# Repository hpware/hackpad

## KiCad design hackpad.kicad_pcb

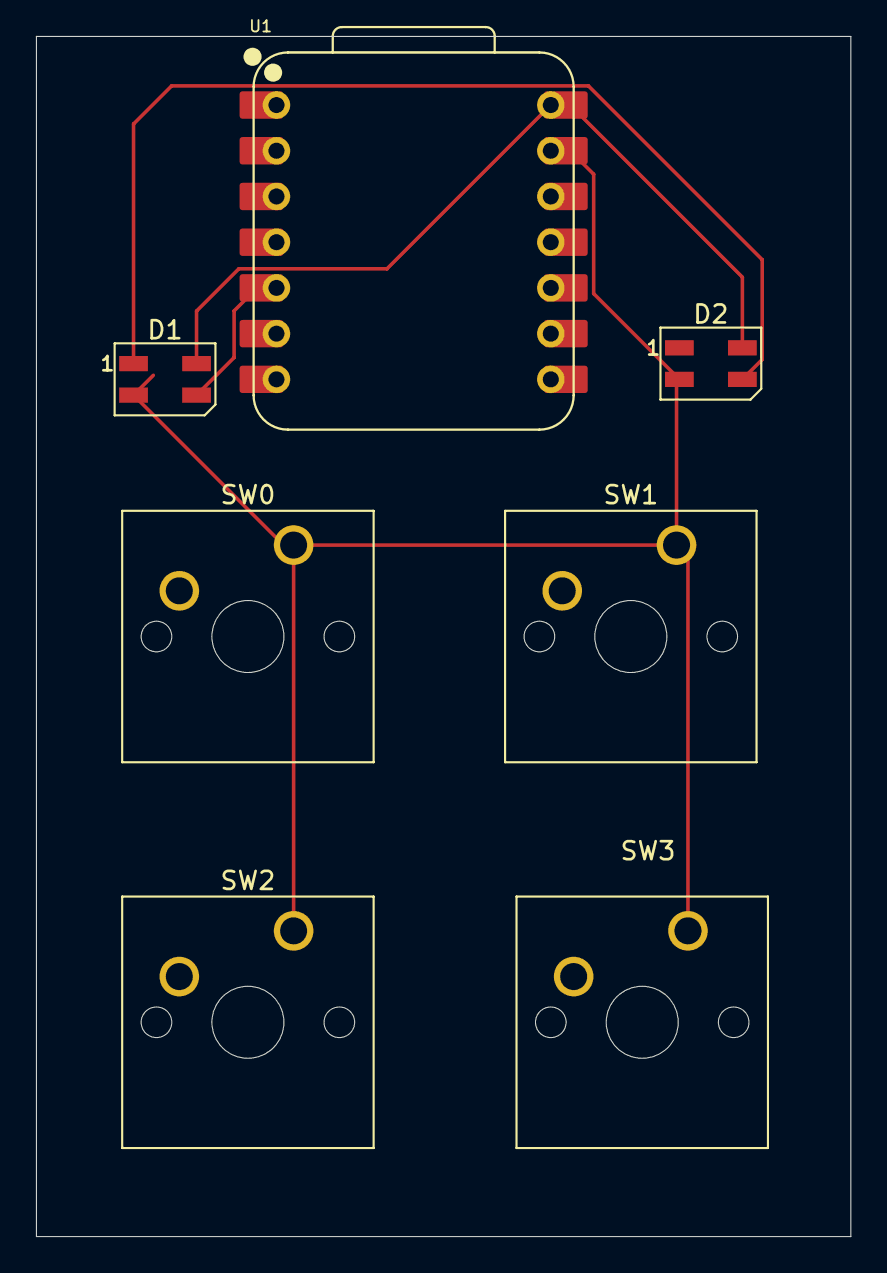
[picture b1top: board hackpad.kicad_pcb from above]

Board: 2 copper layers, 45.2 x 66.7 mm, 7 parts (0 on the bottom side), 8 nets.

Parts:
D1, D2: SK6812MINI; LED_SK6812MINI_PLCC4_3.5x3.5mm_P1.75mm
SW0, SW1, SW2, SW3: SW_Push; SW_Cherry_MX_1.00u_PCB
U1: XIAO-RP2040-DIP

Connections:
+5V: D1.4 (VDD), D2.4 (VDD), U1.14 (VBUS)
GND: D1.2 (VSS), D2.2 (VSS), SW0.1, SW1.1, SW2.1, SW3.1, U1.13 (GND)
unnamed: D1.3 (DIN), U1.5 (GPIO6/SDA)
unnamed: D1.1 (DOUT), D2.3 (DIN)
unnamed: SW0.2, U1.8 (GPIO1/RX)
unnamed: SW1.2, U1.9 (GPIO2/SCK)
unnamed: SW3.2, U1.11 (GPIO3/MOSI)
unnamed: SW2.2, U1.10 (GPIO4/MISO)

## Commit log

2025-06-13 Init
2025-06-13 Do more stuff & Add gitignore & pcb stuff.
2025-06-13 幹，I don't like kicad, 我用到沒有耐心了，我也有強迫症，沒有對齊就更本做不下去啊
